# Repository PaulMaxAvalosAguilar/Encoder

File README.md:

# Encoder2

Connecting science and technology with sport

If you want to achive change you must get power.Objectively know what you do, to control what you get, don't let things happen to you, make things happen.
Be stronger at any weight.

We understand that power is the only way to achieve change. Objectively know what you do, to control what you get. Be stronger at any weight

Incremental Optical Encoder

Project currently being worked by

Paul Max Avalos Aguilar and Ernesto José Quiroz Vázquez ( with the big help
in machine operation of Jose Manuel Peralta Nolasco)

In the aiming of building an optical incremental encoder for vbt trainning

STUDIES THAT CONFIRM RELATIONSHIP BETWEEN VELOCITY AND %RM
Movement Velocity as a Measure of Loading Intensity in Resistance Training
https://www.researchgate.net/publication/41549227_Movement_Velocity_as_a_Measure_of_Loading_Intensity_in_Resistance_Training
There's a load-velocity relationship regardless of individual relative strength. These results confirm an inextricable relationshipbetween relative load and MPV:

1) evaluate maximal strength without the need to perform a 1RM test, or test of maximum number of repetitions to failure (XRM)
2) determine the %1RM that is being used as soon as the first repetition with any given load is performed
3) prescribe and monitor training load according to velocity, instead of percentages of 1RM or XRM.

STUDIES THAT CONFIRM RELATIONSHIP BETWEEN VELOCITY LOSS AND FATIGUE
Effect of loading on unintentional lifting velocity declines during single sets of repetitions to failure during upper and lower extremity muscle actions.
https://www.ncbi.nlm.nih.gov/pubmed/16944400
While average repetition velocity was recorded, a pattern of reduciton in the average velocity achieved during each repetition
was found.
This pattern of average velocity reduction indicates that for a given muscle action fatigue develops between each rep in a
given set in the form of velocity loss

Velocity Loss as a Variable for Monitoring Resistance Exercise
https://www.researchgate.net/publication/313686918_Velocity_Loss_as_a_Variable_for_Monitoring_Resistance_Exercise
There is a very close relationship was found between the relative loss of velocity in a set and the percentage of performed repetitions. Moreover, the percentage of performed repetitions for a given velocity loss showed a high absolute reliability. 

Movement velocity as a measure of level of effort during resistance exercise
https://www.researchgate.net/publication/318150104_Movement_velocity_as_a_measure_of_level_of_effort_during_resistance_exercise
By monitoring repetition velocity one can estimate with high accuracy the proximity of muscle failure and, therefore, to more objectively quantify the level of effort and fatigue being incurred during resistance training.

STUDIES THAT CONFIRM DIFFERENT FATIGUE PERCENTAGES TO GAINS STRENGTH
RESEARCHED APPLICATIONS OF VELOCITY BASED STRENGTH TRAINING
https://pdfs.semanticscholar.org/5f96/79c3f0f2d34478121d7cc33a50eb84dafb7a.pdf
minimizing velocity loss to an inferior to 20 percent can positively influence muscular strength, velocity losses of 35 percent an more can increase metabolites which
might produce longer recovery times

STUDIES THAT CONFIRM LIFTING AT MAX INTENDED SPEED PROVIDES BETTER ADAPTATIONS
Maximal intended velocity training induces greater gains in bench press performance than deliberately slower half-velocity training.
https://www.ncbi.nlm.nih.gov/pubmed/24734902
Lifting a given weight at maximum intended velocity provides significantly greater strength gains.
Strength gains can be maximised when repetitions are performed at maximal intended velocity

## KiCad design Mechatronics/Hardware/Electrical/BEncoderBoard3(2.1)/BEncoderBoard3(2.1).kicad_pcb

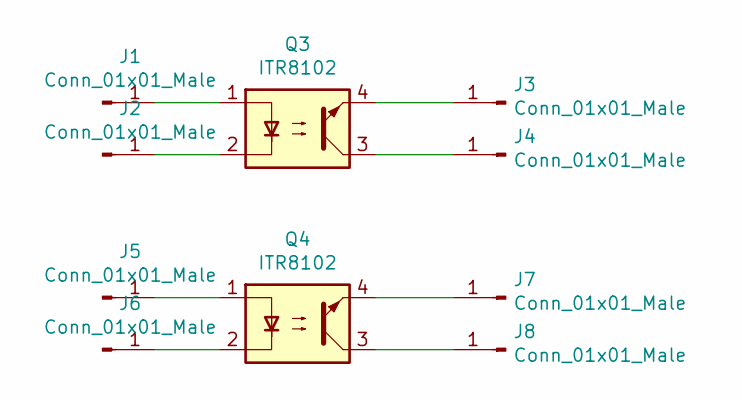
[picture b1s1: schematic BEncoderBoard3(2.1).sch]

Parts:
J1, J2, J3, J4, J5, J6, J7, J8: Conn_01x01_Male; PinHeader_1x01_P2.54mm_Vertical_NO3D
Q3, Q4: ITR8102; itr8102

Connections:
unnamed: J1.1, Q3.1
unnamed: J2.1, Q3.2
unnamed: J3.1, Q3.4
unnamed: J4.1, Q3.3
unnamed: J5.1, Q4.1
unnamed: J6.1, Q4.2
unnamed: J7.1, Q4.4
unnamed: J8.1, Q4.3

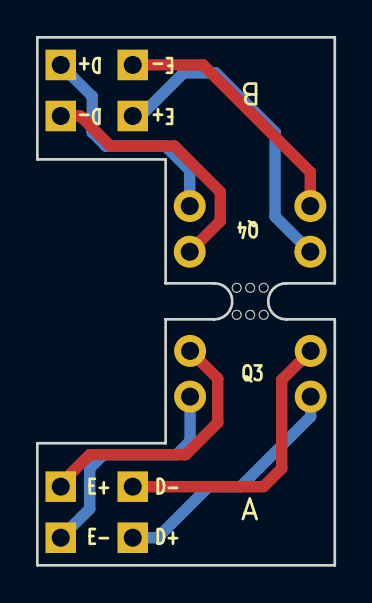
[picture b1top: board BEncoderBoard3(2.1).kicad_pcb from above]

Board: 2 copper layers, 16.5 x 29.3 mm, 11 parts (0 on the bottom side), 8 nets.

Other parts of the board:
mouse-bite-2mm-slot: VAL**; mouse-bite-2mm-slot

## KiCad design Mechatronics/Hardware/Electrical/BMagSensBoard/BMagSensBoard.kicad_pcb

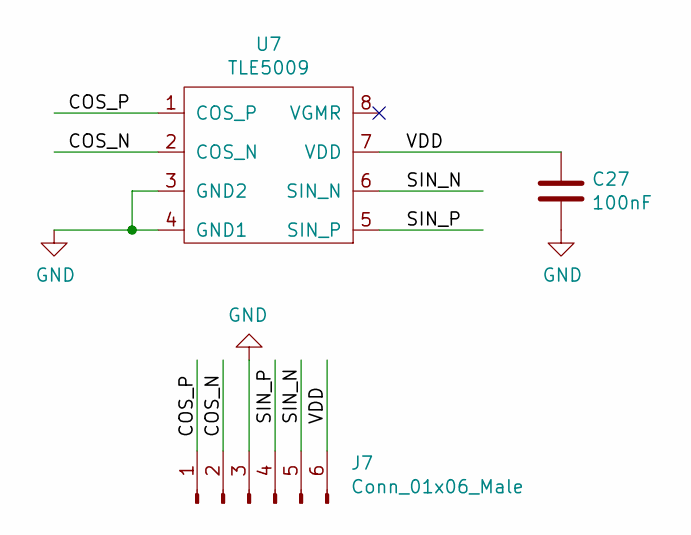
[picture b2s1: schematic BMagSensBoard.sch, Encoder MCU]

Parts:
C27: 100nF; C_0603_1608Metric_Pad1.05x0.95mm_HandSolder
J7: Conn_01x06_Male; SolderWirePad_1x01_SMD_5x10mm
U7: TLE5009; SO-8_3.9x4.9mm_P1.27mm

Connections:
/COS_N: J7.2, U7.2 (COS_N)
/COS_P: J7.1, U7.1 (COS_P)
/SIN_N: J7.5, U7.6 (SIN_N)
/SIN_P: J7.4, U7.5 (SIN_P)
/VDD: C27.1, J7.6, U7.7 (VDD)
GND: C27.2, J7.3, U7.3 (GND2), U7.4 (GND1)

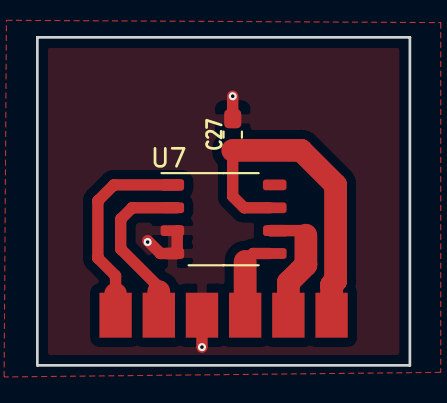
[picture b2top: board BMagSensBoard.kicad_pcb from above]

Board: 2 copper layers, 20.7 x 18.2 mm, 3 parts (0 on the bottom side), 6 nets.

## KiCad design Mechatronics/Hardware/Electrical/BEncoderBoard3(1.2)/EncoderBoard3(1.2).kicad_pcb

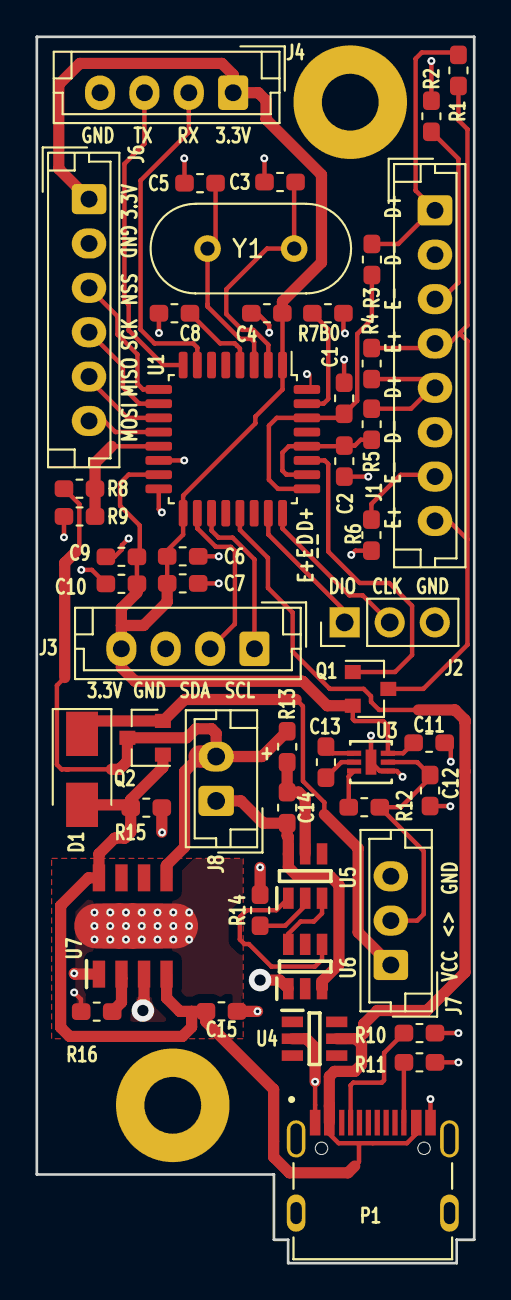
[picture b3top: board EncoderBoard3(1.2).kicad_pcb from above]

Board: 2 copper layers, 24.6 x 69.1 mm, 51 parts (0 on the bottom side), 40 nets.

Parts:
C1, C2: C; C_0603_1608Metric_Pad1.05x0.95mm_HandSolder
C3, C5: 12pF; C_0603_1608Metric_Pad1.05x0.95mm_HandSolder
C4, C6, C8, C14: 100nF; C_0603_1608Metric_Pad1.05x0.95mm_HandSolder
C7, C11: 4.7uF; C_0603_1608Metric_Pad1.05x0.95mm_HandSolder
C9: 10nF; C_0603_1608Metric_Pad1.05x0.95mm_HandSolder
C10, C12, C13: 1uF; C_0603_1608Metric_Pad1.05x0.95mm_HandSolder
C15: 10uF; C_0603_1608Metric_Pad1.05x0.95mm_HandSolder
D1: D; D_SMA
H1, H2: MountingHole_Pad; MountingHole_3.2mm_M3_Pad
J1: Conn_01x08_Male; JST_EH_B8B-EH-A_1x08_P2.50mm_Vertical
J2: Conn_01x03_Male; PinHeader_1x03_P2.54mm_Vertical
J3, J4: Conn_01x04_Male; JST_EH_B4B-EH-A_1x04_P2.50mm_Vertical
J6: Conn_01x06_Male; JST_EH_B6B-EH-A_1x06_P2.50mm_Vertical
J7: Conn_01x03_Male; JST_EH_B3B-EH-A_1x03_P2.50mm_Vertical
J8: Conn_01x02_Male; JST_EH_B2B-EH-A_1x02_P2.50mm_Vertical
P1: TYPE-C-31-M-12; HRO_TYPE-C-31-M-12
Q1, Q2: Q_PMOS_GSD; SOT-23
R1, R4: 1.2K; R_0603_1608Metric_Pad1.05x0.95mm_HandSolder
R2, R6: 560; R_0603_1608Metric_Pad1.05x0.95mm_HandSolder
R3, R5: R; R_0603_1608Metric_Pad1.05x0.95mm_HandSolder
R7, R8, R9, R12, R15: 10K; R_0603_1608Metric_Pad1.05x0.95mm_HandSolder
R10: 5.1k; R_0603_1608Metric_Pad1.05x0.95mm_HandSolder
R11: 5.1K; R_0603_1608Metric_Pad1.05x0.95mm_HandSolder
R13: 100; R_0603_1608Metric_Pad1.05x0.95mm_HandSolder
R14: 1K; R_0603_1608Metric_Pad1.05x0.95mm_HandSolder
R16: 1.5K; R_0603_1608Metric_Pad1.05x0.95mm_HandSolder
U1: STM32G431KBT6; LQFP-32_7x7mm_P0.8mm
U3: LTC3240; DFN-6_DC
U4: 82402305; Sot-23(6)
U5: DW01+G; Sot-23(6)
U6: DMosfet; Sot-23(6)
U7: TP4056; Sop(8)
Y1: 8Mhz; Crystal_HC49-U_Vertical

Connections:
+3V3: C4.1, C6.1, C7.1, C9.1, C10.1, C11.1, J3.4, J4.1, J6.1, Q1.2, U1.1, U1.15, U1.17, U3.3
/BLERX: J4.2, U1.7
/BLETX: J4.3, U1.8
/D+(a): J1.1, R1.2, R3.2
/D+(b): J1.5, R4.2, R5.2
/E+(a): J1.4, J1.8, Q1.3, R1.1, R4.1
/E-(a): J1.3, R2.1
/E-(b): J1.7, R6.1
/EncEnable: Q1.1, U1.27
/I2C2SCL: J3.1, U1.19
/I2C2SDA: J3.2, U1.18
/LPTIM1_IN1: C2.2, R5.1, U1.26, U1.28
/LPTIM1_IN2: C1.1, R3.1, U1.25, U1.30
/SWCLK: J2.2, U1.24
/SWDIO: J2.1, U1.23
/Sens_SPIMISO: J6.5, U1.11
/Sens_SPIMOSI: J6.6, U1.12
/Sens_SPINSS: J6.3, U1.9
/Sens_SPISCK: J6.4, U1.10
Batt+: J8.2, Q2.3, R8.1, R13.1, U7.5
Batt-: C14.2, J8.1, U5.6, U6.3
GND: C1.2, C2.1, C3.1, C4.2, C5.1, C6.2, C7.2, C8.2, C9.2, C10.2, C11.2, C12.1, C15.2, H1.1, H2.1, J1.2, J1.6, J2.3, J3.3, J4.4, J6.2, J7.3, P1.A1B12, P1.B1A12, P1.S1, P1.S2, P1.S3, P1.S4, R2.2, R6.2, R7.2, R9.2, R10.2, R11.2, R14.2, R15.2, R16.2, U1.14, U1.16, U1.32, U3.1, U3.7, U4.2, U6.1, U7.1, U7.3, U7.9
unnamed: C3.2, U1.2, Y1.2
unnamed: C5.2, U1.3, Y1.1
unnamed: C8.1, U1.4
unnamed: C12.2, J7.2, R12.1, U3.2
unnamed: C13.1, U3.5
unnamed: C13.2, U3.4
unnamed: C14.1, R13.2, U5.5
unnamed: D1.1, J7.1, Q2.2
unnamed: P1.A5, R10.1
unnamed: P1.B5, R11.1
unnamed: R7.1, U1.31
unnamed: R8.2, R9.1, U1.13
unnamed: R12.2, U3.6
unnamed: R14.1, U5.2
unnamed: R16.1, U7.2
unnamed: U5.1, U6.4
unnamed: U5.3, U6.6
VCC: C15.1, D1.2, P1.A4B9, P1.B4A9, Q2.1, R15.1, U1.21, U4.5, U7.4, U7.8

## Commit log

2019-02-25 Untracked files
2019-03-03 New efficieny algorithm added
2019-03-04 Moved test functions to a signle file
2019-03-05 Adapted code to Arduino working
2019-03-10 Added more efficient algorithm
2019-03-10 Full new high efficiency algorithm implementation
2019-03-10 Added line separators to bluetooth communication
2019-03-10 Added unsigned integer implementation
2019-03-14 Added low percent error version
2019-03-16 Added header modifications aware makefile instructions
2019-03-16 Added variables
2019-03-17 Added high precition ArmCortex Version
2019-03-17 ArmCortex cpp makefile finished
2019-03-28 Added c/c++ integration
2023-01-31 Added thread safe printf support
2023-01-31 Added doc file
2023-01-31 Added directions
2023-01-31 Advances for Sensor Positioning
2023-01-31 Working changes
2023-01-31 Advances
2023-01-31 Added drawings
2023-01-31 Finished advances
2023-01-31 Apparently finished
2023-01-31 Model corrected
2023-01-31 Finished Encoder design
2023-01-31 Modified name
2023-01-31 Added Fillets
2023-01-31 Added changes
2023-01-31 Final changes
2023-01-31 Useful advances
2023-01-31 Added documentation
2023-01-31 Added changes and modified files
2023-01-31 Modified files
2023-01-31 Added files
2023-01-31 Added timer configuration
2023-01-31 Added data
2023-01-31 Added timer functionality
2023-01-31 Finished changes
2023-01-31 Important changes
2023-01-31 Added file from Windows
2023-01-31 Changed gitignore
2023-01-31 Added libraries
2023-01-31 Added changes to Freecad design
2023-01-31 Added instructive
2023-01-31 Finally functional bluetooth
2023-01-31 Added SensorsBoard Gerbers
2023-01-31 Modified uart(FUNCTIONAL)
2023-01-31 Board Changes
2023-01-31 Added QueueSet communication task functionality
2023-01-31 Added commentaries
2023-01-31 Updated changes
2023-01-31 Modified ABISoftware (App)
2023-01-31 Added first message receiving logic
2023-01-31 Added ble sleep functionality
2023-01-31 Changes for characteristic writing
2023-01-31 Scanning changes
2023-01-31 Added low power features
2023-01-31 Added 2d and 3d images
2023-01-31 Added changes to speed and repetition algorithm
2023-01-31 Mean propulsive algorithm added
2023-01-31 Encoder Task Changes (Velocity calculation algorithm
2023-01-31 Encoder parameters code
2023-01-31 Interface changes
2023-01-31 Added aparent final changes
2023-01-31 Added changes without timer error
2023-01-31 Battery charging status finalized
2023-01-31 Apparently timer problem solved
2023-01-31 Added new Support
2023-01-31 Added instructions
2023-01-31 Instructive changed
2023-01-31 Characterization
2023-01-31 Mechanical Changes
2023-01-31 Final changes to 3d model
2023-01-31 Added debugging capabilities
2023-01-31 Added debug functionality
2023-01-31 Change
2023-01-31 New Formula
2023-01-31 Added cosine/sine function
2023-01-31 Added lib
2023-01-31 New Calculations
2023-01-31 Units measurment added
2023-01-31 New Changes
2023-01-31 Additions
2023-01-31 Change s
2023-01-31 Finished PCB
2023-01-31 Finished board png
2023-01-31 Schematic change
2023-01-31 Final PCB
2023-01-31 Magnetic sensors board done
2023-01-31 Deleted KiBoM & BOM generated
2023-01-31 Moved directory
2023-01-31 Removed csv
2023-01-31 Reuploaded pcb
2023-01-31 Added Gerbers
2023-01-31 Added gerber files
2023-01-31 Changed name
2023-01-31 Changed files
2023-01-31 Changed directory
2023-01-31 pin header change
2023-01-31 Recreated gerbers
2023-01-31 Changed panelization shape
2023-01-31 Introduced G4 code
2023-01-31 Add changes
2023-01-31 Corrections applied
2023-01-31 Added I2C configuration
2023-01-31 Changes for bluetooth programmer code
2023-01-31 Checked PLL functioning
2023-01-31 Added debug capabilities
2023-01-31 Added UART
2023-01-31 Added USART basic configuration
2023-01-31 Added semihosting
2023-01-31 Upgrades for dma
2023-01-31 Added DMA transmit
2023-01-31 Added DMA receive
2023-01-31 Added I2C functionality
2023-01-31 LCD pre DMA
2023-01-31 Added LCD puts function improvement
2023-01-31 Added I2C DMA
2023-01-31 Added encoder mode
2023-01-31 Added timer interrupt functionality
2023-01-31 Added charging detection capabilities
2023-01-31 Added lpr correction
2023-01-31 Added low power functionality
2023-01-31 Added corrections to software
2023-01-31 Added pin testing
2023-01-31 Added rtos
2023-01-31 Added ADC code
2023-01-31 Vrefbuf addition
2023-01-31 Added ADC clean oversampler
2023-01-31 Added CORDIC capabilities
2023-01-31 Added tim2 changes
2023-01-31 Parsing capabilities refined
2023-01-31 Added RXTask
2023-01-31 LCD task advances
2023-01-31 adc code added
2023-01-31 Encoder Parsing capabilities added
2023-01-31 Added encoder protocol
2023-01-31 Added new protocol and uartTXQueue
2023-01-31 Custom functions folder and Timer initialization added
2023-01-31 Added uartTX protocol
2023-01-31 tickless idle functionality infrastructure added
2023-01-31 Added decode bytes helper function
2023-01-31 changed function name
2023-01-31 Added encoder task and adc redesign improvements
2023-01-31 Added super improved version
2023-01-31 Added adc suspension
2023-01-31 Added task notifications
2023-01-31 Added void parameters for encoderTask
2023-01-31 Improved LCD library
2023-01-31 Changed FreeRTOS version
2023-01-31 Added missing files
2023-01-31 Modernized task
2023-01-31 Improvements
2023-01-31 Encoder Task finally finished (thank's God)
2023-01-31 Removed spurious emacs files
2023-01-31 Removed unnecesary openocd binaries and dll's
2023-01-31 Changed names
2023-01-31 Added custom functions
2023-01-31 Changed uart directory
2023-01-31 Removed UART double ring architecture
2023-01-31 Added receive new protocol implementation
2023-01-31 Added new communication protocol implementation
2023-01-31 Standarization
2023-01-31 Added updates
2023-01-31 Added format for main.h
2023-01-31 Added format to protocol
2023-01-31 Added new naming and rules
2023-01-31 New description and naming
2023-01-31 Nonworking
2023-01-31 Charging status implemented, stack problem solved
2023-01-31 Finished rev 1 device
2023-01-31 Dummy commit
2023-01-31 PCB changes
2023-01-31 Non plus ultra changes
2023-01-31 Mass production changes
2023-02-23 New Mechanical Parts added
2023-07-18 Work in progress
2023-07-30 Working solution: revert to this if something fails
2023-07-31 Working progress
2023-07-31 (Working) Encoder Hal module advances
